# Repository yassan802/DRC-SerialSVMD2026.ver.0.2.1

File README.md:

STS3215等のシリアルバスサーボを動かすための基板。ver.0.1.2からの変更点としては、基板サイズが45*60mmになったこと、マイコンがRP2354Aになったこと、動力用電源に5Vを使用できることなどがあげられる。  
ver.0.1.2 → https://github.com/kotek-7/DRC-SerialSVMD2026/

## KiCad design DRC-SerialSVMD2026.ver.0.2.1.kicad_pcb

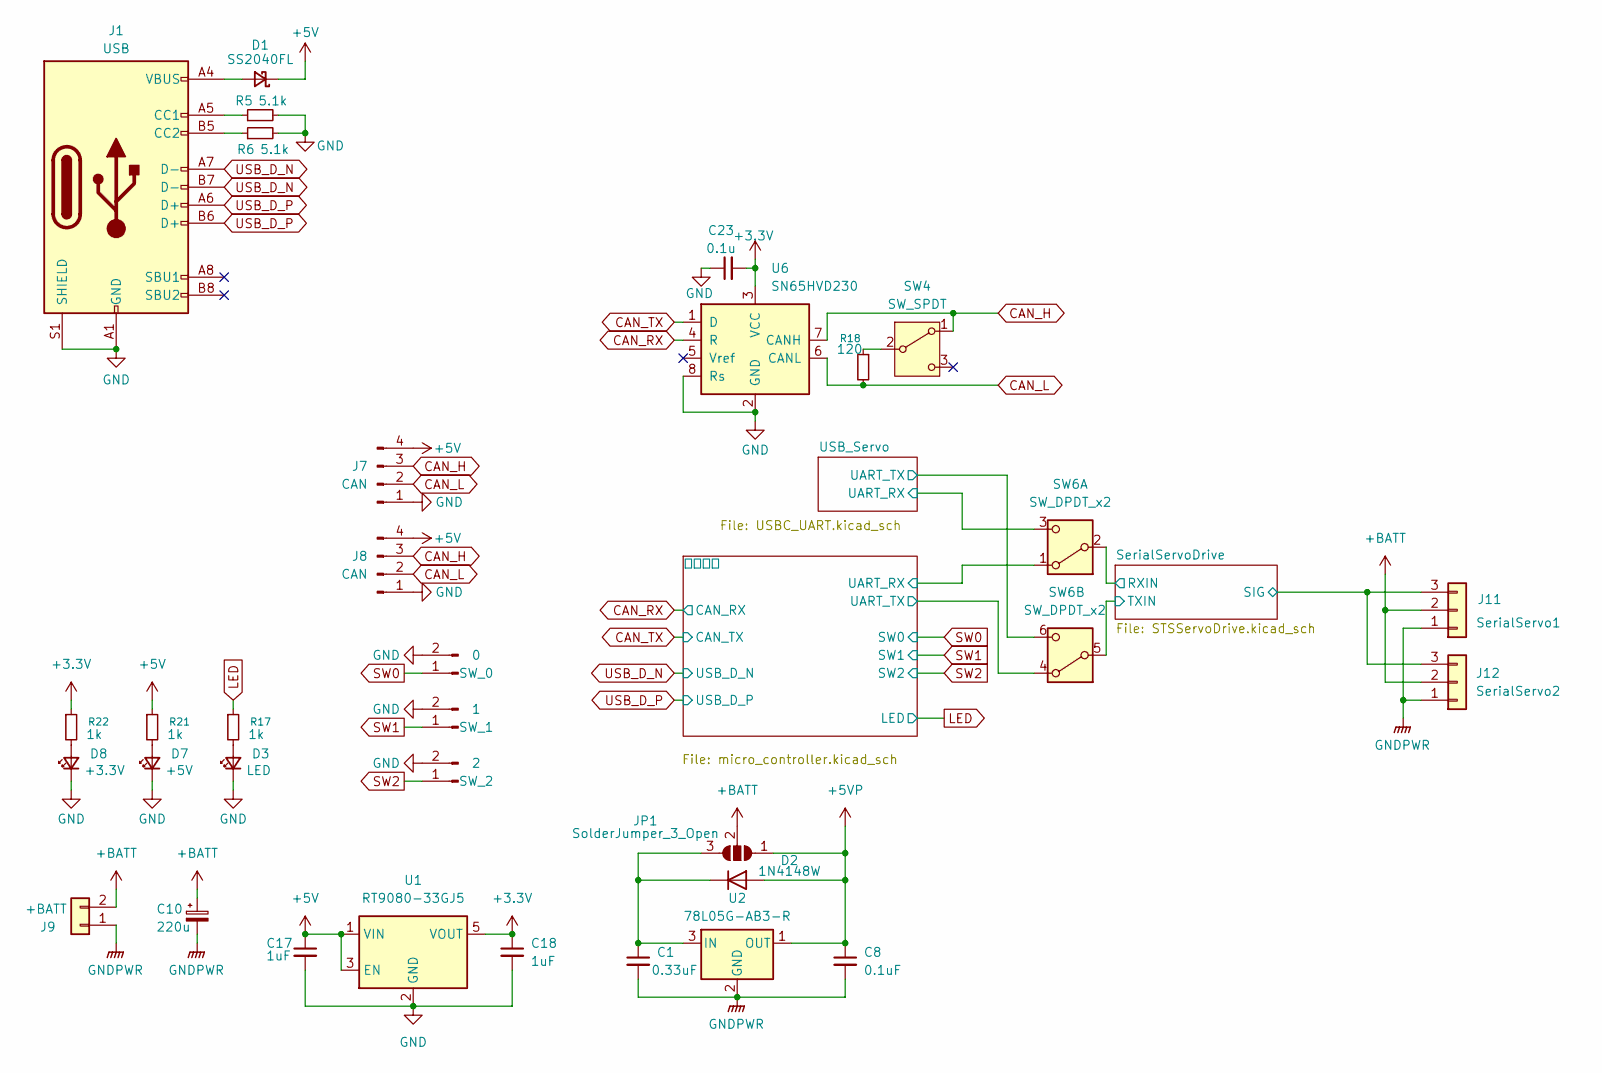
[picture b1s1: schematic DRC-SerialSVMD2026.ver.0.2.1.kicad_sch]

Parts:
C1: 0.33uF; C_0603_1608Metric_Pad1.08x0.95mm_HandSolder
C8: 0.1uF; C_0603_1608Metric_Pad1.08x0.95mm_HandSolder
C10: 220u; CP_Radial_D8.0mm_P3.50mm
C17, C18: 1uF; C_0603_1608Metric_Pad1.08x0.95mm_HandSolder
C23: 0.1u; C_0603_1608Metric_Pad1.08x0.95mm_HandSolder
D1: SS2040FL; D_SOD-123F
D2: 1N4148W; D_SOD-123
D3: LED; LED_0603_1608Metric_Pad1.05x0.95mm_HandSolder
D7: +5V; LED_0603_1608Metric_Pad1.05x0.95mm_HandSolder
D8: +3.3V; LED_0603_1608Metric_Pad1.05x0.95mm_HandSolder
J1: USB; USB_C_Receptacle_GCT_USB4105-xx-A_16P_TopMnt_Horizontal
J7, J8: CAN; JST_XH_S4B-XH-A_1x04_P2.50mm_Horizontal
J9: +BATT; AMASS_XT30PW-M_1x02_P2.50mm_Horizontal
J11: SerialServo1; JST_XH_S3B-XH-A_1x03_P2.50mm_Horizontal
J12: SerialServo2; JST_XH_S3B-XH-A_1x03_P2.50mm_Horizontal
JP1: SolderJumper_3_Open; SolderJumper-3_P1.3mm_Open_RoundedPad1.0x1.5mm_NumberLabels
R5, R6: 5.1k; R_0603_1608Metric_Pad0.98x0.95mm_HandSolder
R17, R21, R22: 1k; R_0603_1608Metric_Pad0.98x0.95mm_HandSolder
R18: 120; R_0603_1608Metric_Pad0.98x0.95mm_HandSolder
SW4: SW_SPDT; SW_Slide_SS-12D00G3_1P2T_P2.50mm
SW6: SW_DPDT_x2; IS-2235-G
SW_0: 0; JST_XH_B2B-XH-A_1x02_P2.50mm_Vertical
SW_1: 1; JST_XH_B2B-XH-A_1x02_P2.50mm_Vertical
SW_2: 2; JST_XH_B2B-XH-A_1x02_P2.50mm_Vertical
U1: RT9080-33GJ5; TSOT-23-5_HandSoldering
U2: 78L05G-AB3-R; SOT-89-3
U6: SN65HVD230; SOIC-8_3.9x4.9mm_P1.27mm

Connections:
+3.3V: C18.1, C23.2, R22.1, U1.5 (VOUT), U6.3 (VCC); also elsewhere on the board
+5V: C17.1, D1.1 (K), J7.4, J8.4, R21.1, U1.1 (VIN), U1.3 (EN); also elsewhere on the board
+5VP: C8.1, D2.2 (A), JP1.1 (A), U2.1 (OUT); also elsewhere on the board
+BATT: C10.1, J9.2, J11.2, J12.2, JP1.2 (C)
/SerialServoDrive/RXIN: SW6.2 (B); also elsewhere on the board
/SerialServoDrive/SIG: J11.3, J12.3; also elsewhere on the board
/SerialServoDrive/TXIN: SW6.5 (B); also elsewhere on the board
/USB_Servo/UART_RX: SW6.3 (C); also elsewhere on the board
/USB_Servo/UART_TX: SW6.6 (C); also elsewhere on the board
/マイコン/UART_RX: SW6.1 (A); also elsewhere on the board
/マイコン/UART_TX: SW6.4 (A); also elsewhere on the board
CAN_H: J7.3, J8.3, SW4.1 (A), U6.7 (CANH)
CAN_L: J7.2, J8.2, R18.2, U6.6 (CANL)
CAN_RX: U6.4 (R); also elsewhere on the board
CAN_TX: U6.1 (D); also elsewhere on the board
GND: C17.2, C18.2, C23.1, D3.1 (K), D7.1 (K), D8.1 (K), J1.A1 (GND), J1.A12 (GND), J1.B1 (GND), J1.B12 (GND), J1.S1 (SHIELD), J7.1, J8.1, R5.2, R6.2, SW_0.2, SW_1.2, SW_2.2, U1.2 (GND), U6.2 (GND), U6.8 (Rs); also elsewhere on the board
GNDPWR: C1.2, C8.2, C10.2, J9.1, J11.1, J12.1, U2.2 (GND); also elsewhere on the board
LED: R17.1; also elsewhere on the board
unnamed: D1.2 (A), J1.A4 (VBUS), J1.A9 (VBUS), J1.B4 (VBUS), J1.B9 (VBUS)
unnamed: C1.1, D2.1 (K), JP1.3 (B), U2.3 (IN)
unnamed: D3.2 (A), R17.2
unnamed: D7.2 (A), R21.2
unnamed: D8.2 (A), R22.2
unnamed: J1.A5 (CC1), R5.1
unnamed: J1.B5 (CC2), R6.1
unnamed: R18.1, SW4.2 (B)
SW0: SW_0.1; also elsewhere on the board
SW1: SW_1.1; also elsewhere on the board
SW2: SW_2.1; also elsewhere on the board
USB_D_N: J1.A7 (D-), J1.B7 (D-); also elsewhere on the board
USB_D_P: J1.A6 (D+), J1.B6 (D+); also elsewhere on the board

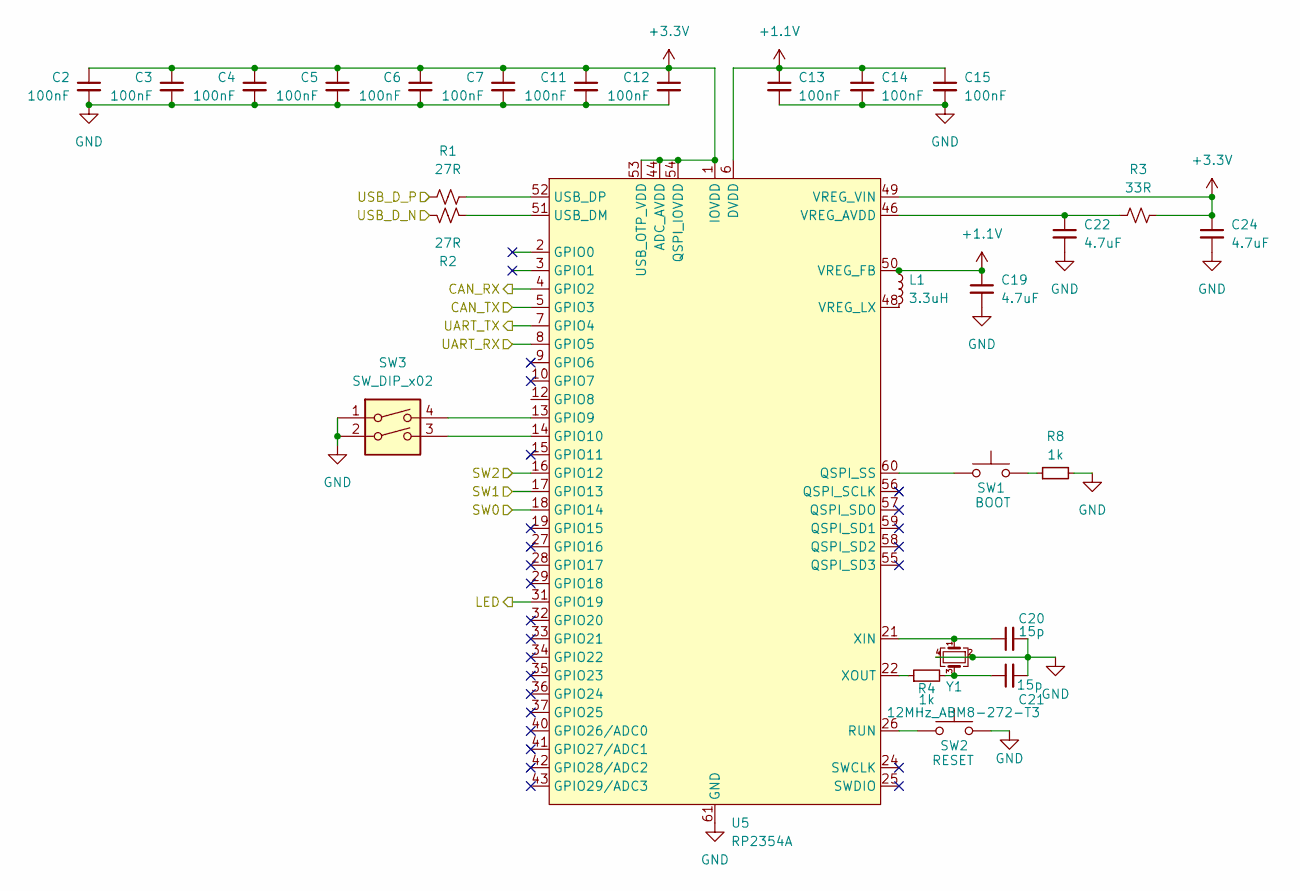
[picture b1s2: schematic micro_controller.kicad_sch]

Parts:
C2, C3, C4, C5, C6, C7, C11, C12, C13, C14, C15: 100nF; C_0603_1608Metric_Pad1.08x0.95mm_HandSolder
C19, C22, C24: 4.7uF; C_0603_1608Metric
C20, C21: 15p; C_0402_1005Metric
L1: 3.3uH; abracon_aota-b201610s3r3-101-t
R1, R2: 27R; R_0603_1608Metric
R3: 33R; R_0402_1005Metric
R4: 1k; R_0402_1005Metric
R8: 1k; R_0603_1608Metric_Pad0.98x0.95mm_HandSolder
SW1: BOOT; SW_TS-1088-AR02016
SW2: RESET; SW_TS-1088-AR02016
SW3: SW_DIP_x02; SW_DIP_SPSTx02_Slide_KingTek_DSHP02TS_W7.62mm_P1.27mm
U5: RP2354A; QFN-60-1EP_7x7mm_P0.4mm_EP3.4x3.4mm_ThermalVias
Y1: 12MHz_ABM8-272-T3; generic_xtalcc320x250x80-4

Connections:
+1.1V: C13.1, C14.1, C15.1, C19.1, L1.1, U5.6 (DVDD), U5.23 (DVDD), U5.39 (DVDD), U5.50 (VREG_FB)
+3.3V: C2.1, C3.1, C4.1, C5.1, C6.1, C7.1, C11.1, C12.1, C24.1, R3.2, U5.1 (IOVDD), U5.11 (IOVDD), U5.20 (IOVDD), U5.30 (IOVDD), U5.38 (IOVDD), U5.44 (ADC_AVDD), U5.45 (IOVDD), U5.49 (VREG_VIN), U5.53 (USB_OTP_VDD), U5.54 (QSPI_IOVDD); also elsewhere on the board
/マイコン/UART_RX: U5.8 (GPIO5); also elsewhere on the board
/マイコン/UART_TX: U5.7 (GPIO4); also elsewhere on the board
CAN_RX: U5.4 (GPIO2); also elsewhere on the board
CAN_TX: U5.5 (GPIO3); also elsewhere on the board
GND: C2.2, C3.2, C4.2, C5.2, C6.2, C7.2, C11.2, C12.2, C13.2, C14.2, C15.2, C19.2, C20.2, C21.2, C22.2, C24.2, R8.2, SW2.1, SW3.1, SW3.2, U5.47 (VREG_PGND), U5.61 (GND), Y1.2, Y1.4; also elsewhere on the board
LED: U5.31 (GPIO19); also elsewhere on the board
unnamed: C21.1, R4.2, Y1.3
unnamed: R8.1, SW1.1
unnamed: SW3.4, U5.13 (GPIO9)
unnamed: SW3.3, U5.14 (GPIO10)
unnamed: SW1.2, U5.60 (QSPI_SS)
unnamed: SW2.2, U5.26 (RUN)
unnamed: R2.2, U5.51 (USB_DM)
unnamed: R1.2, U5.52 (USB_DP)
unnamed: C22.1, R3.1, U5.46 (VREG_AVDD)
unnamed: L1.2, U5.48 (VREG_LX)
unnamed: C20.1, U5.21 (XIN), Y1.1
unnamed: R4.1, U5.22 (XOUT)
SW0: U5.18 (GPIO14); also elsewhere on the board
SW1: U5.17 (GPIO13); also elsewhere on the board
SW2: U5.16 (GPIO12); also elsewhere on the board
USB_D_N: R2.1; also elsewhere on the board
USB_D_P: R1.1; also elsewhere on the board

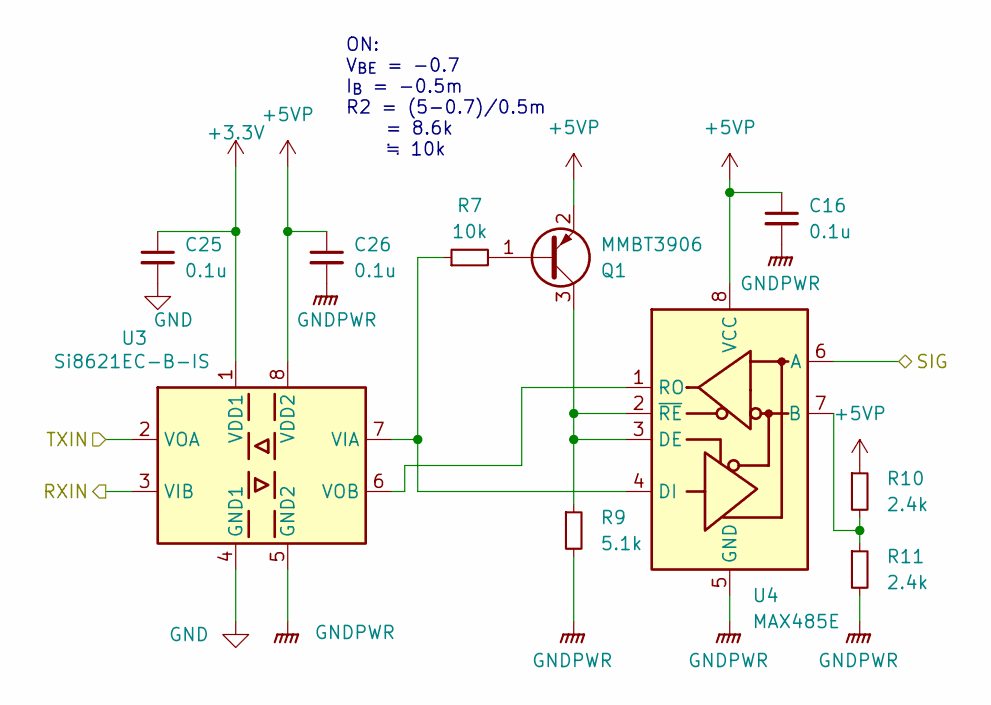
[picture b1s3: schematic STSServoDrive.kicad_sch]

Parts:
C16, C25, C26: 0.1u; C_0603_1608Metric_Pad1.08x0.95mm_HandSolder
Q1: MMBT3906; SOT-23-3; LCSC x
R7: 10k; R_0603_1608Metric_Pad0.98x0.95mm_HandSolder
R9: 5.1k; R_0603_1608Metric_Pad0.98x0.95mm_HandSolder
R10, R11: 2.4k; R_0603_1608Metric_Pad0.98x0.95mm_HandSolder
U3: Si8621EC-B-IS; SOIC-8_3.9x4.9mm_P1.27mm
U4: MAX485E; SOIC-8_3.9x4.9mm_P1.27mm

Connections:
+3.3V: C25.1, U3.1 (VDD1); also elsewhere on the board
+5VP: C16.1, C26.1, Q1.2 (E), R10.1, U3.8 (VDD2), U4.8 (VCC); also elsewhere on the board
/SerialServoDrive/RXIN: U3.3 (VIB); also elsewhere on the board
/SerialServoDrive/SIG: U4.6 (A); also elsewhere on the board
/SerialServoDrive/TXIN: U3.2 (VOA); also elsewhere on the board
GND: C25.2, U3.4 (GND1); also elsewhere on the board
GNDPWR: C16.2, C26.2, R9.2, R11.2, U3.5 (GND2), U4.5 (GND); also elsewhere on the board
unnamed: Q1.1 (B), R7.2
unnamed: Q1.3 (C), R9.1, U4.2 (~RE), U4.3 (DE)
unnamed: R7.1, U3.7 (VIA), U4.4 (DI)
unnamed: U3.6 (VOB), U4.1 (RO)
unnamed: R10.2, R11.1, U4.7 (B)

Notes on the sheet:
ON: V_{BE} = -0.7 I_{B} = -0.5m R2 = (5-0.7)/0.5m = 8.6k ≒ 10k

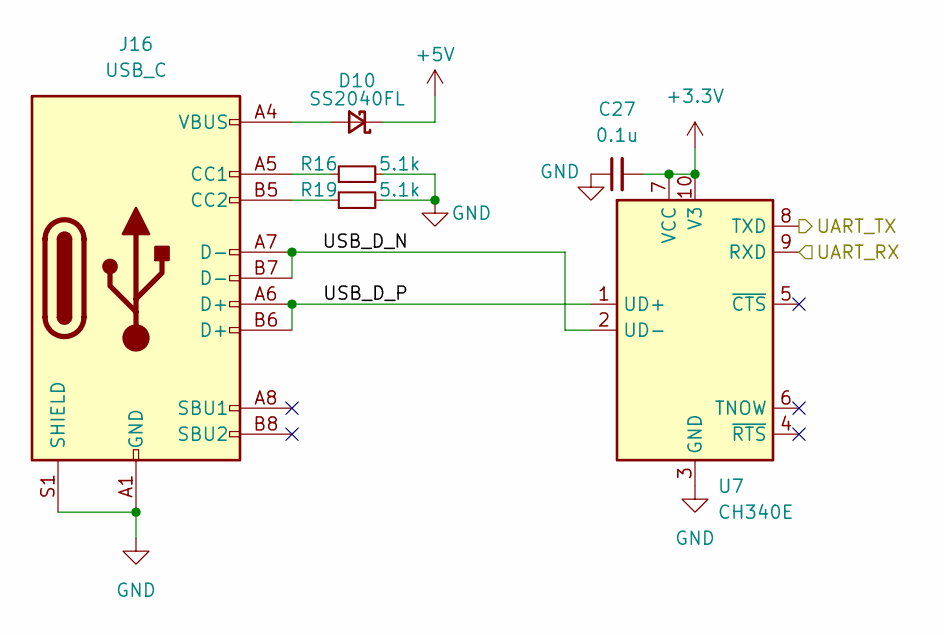
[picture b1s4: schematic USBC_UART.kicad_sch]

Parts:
C27: 0.1u; C_0603_1608Metric_Pad1.08x0.95mm_HandSolder
D10: SS2040FL; D_SOD-123F
J16: USB_C; USB_C_Receptacle_GCT_USB4105-xx-A_16P_TopMnt_Horizontal
R16, R19: 5.1k; R_0603_1608Metric_Pad0.98x0.95mm_HandSolder
U7: CH340E; MSOP-10_3x3mm_P0.5mm

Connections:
+3.3V: C27.2, U7.7 (VCC), U7.10 (V3); also elsewhere on the board
+5V: D10.1 (K); also elsewhere on the board
/USB_Servo/UART_RX: U7.9 (RXD); also elsewhere on the board
/USB_Servo/UART_TX: U7.8 (TXD); also elsewhere on the board
/USB_Servo/USB_D_N: J16.A7 (D-), J16.B7 (D-), U7.2 (UD-)
/USB_Servo/USB_D_P: J16.A6 (D+), J16.B6 (D+), U7.1 (UD+)
GND: C27.1, J16.A1 (GND), J16.A12 (GND), J16.B1 (GND), J16.B12 (GND), J16.S1 (SHIELD), R16.2, R19.2, U7.3 (GND); also elsewhere on the board
unnamed: D10.2 (A), J16.A4 (VBUS), J16.A9 (VBUS), J16.B4 (VBUS), J16.B9 (VBUS)
unnamed: J16.A5 (CC1), R16.1
unnamed: J16.B5 (CC2), R19.1

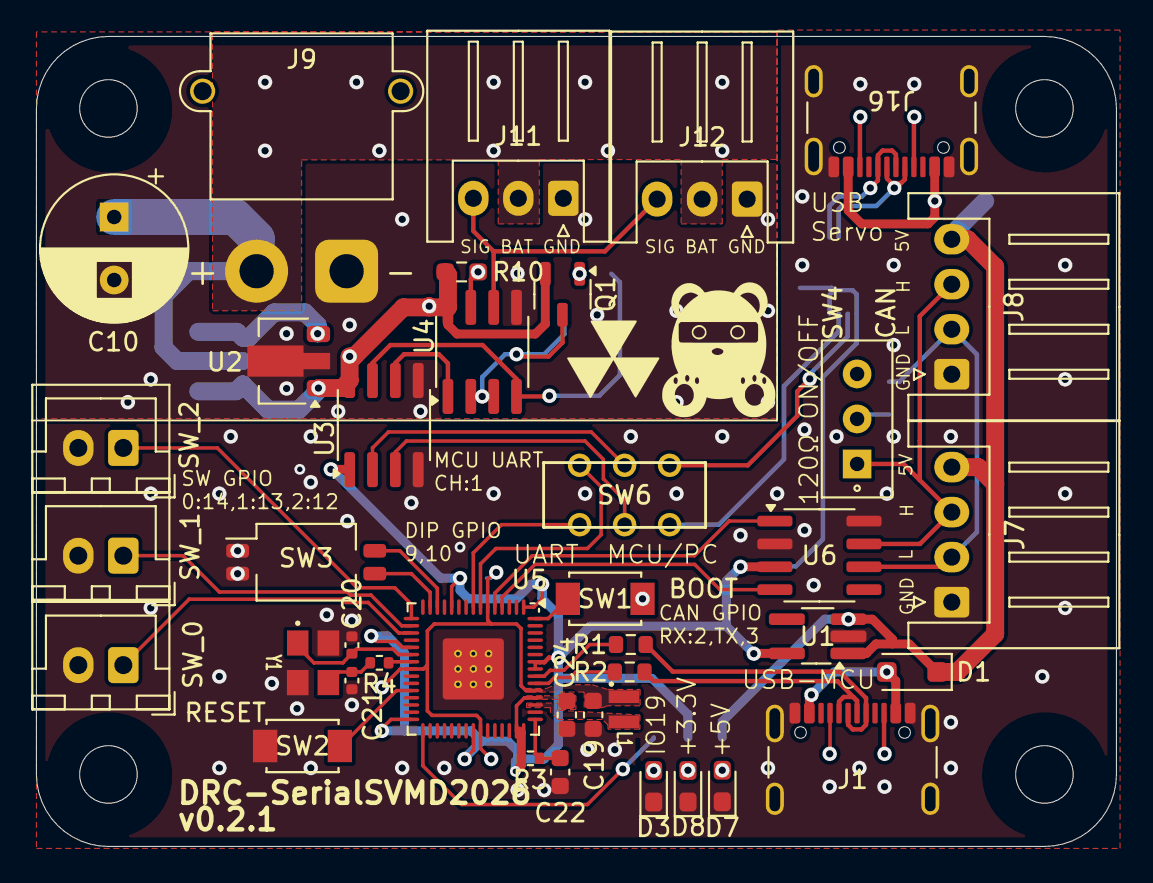
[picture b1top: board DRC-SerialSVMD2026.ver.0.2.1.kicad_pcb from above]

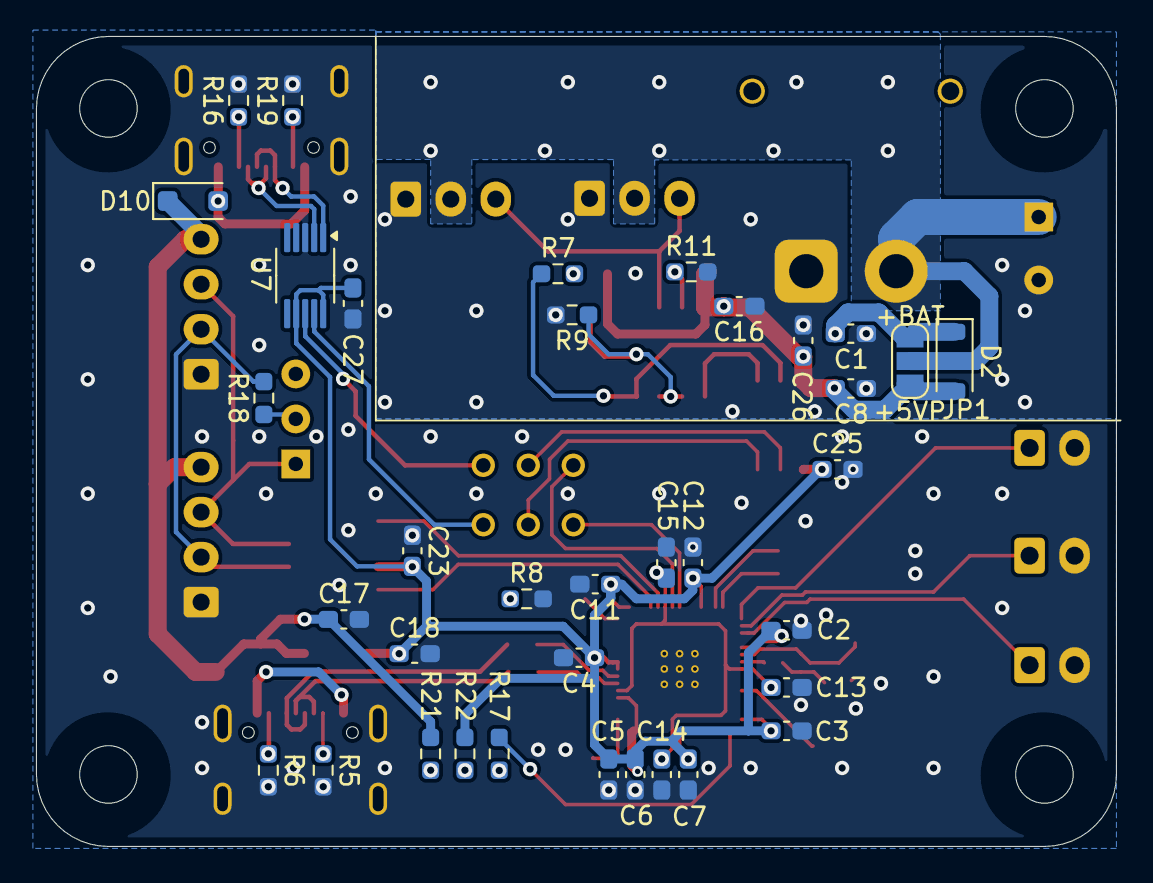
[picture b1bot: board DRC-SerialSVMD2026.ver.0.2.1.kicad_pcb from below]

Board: 2 copper layers, 60.0 x 45.0 mm, 75 parts (36 on the bottom side), 54 nets.
